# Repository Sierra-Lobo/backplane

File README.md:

# backplane

Sierra Lobo's 1.5U Cubesat Backplane

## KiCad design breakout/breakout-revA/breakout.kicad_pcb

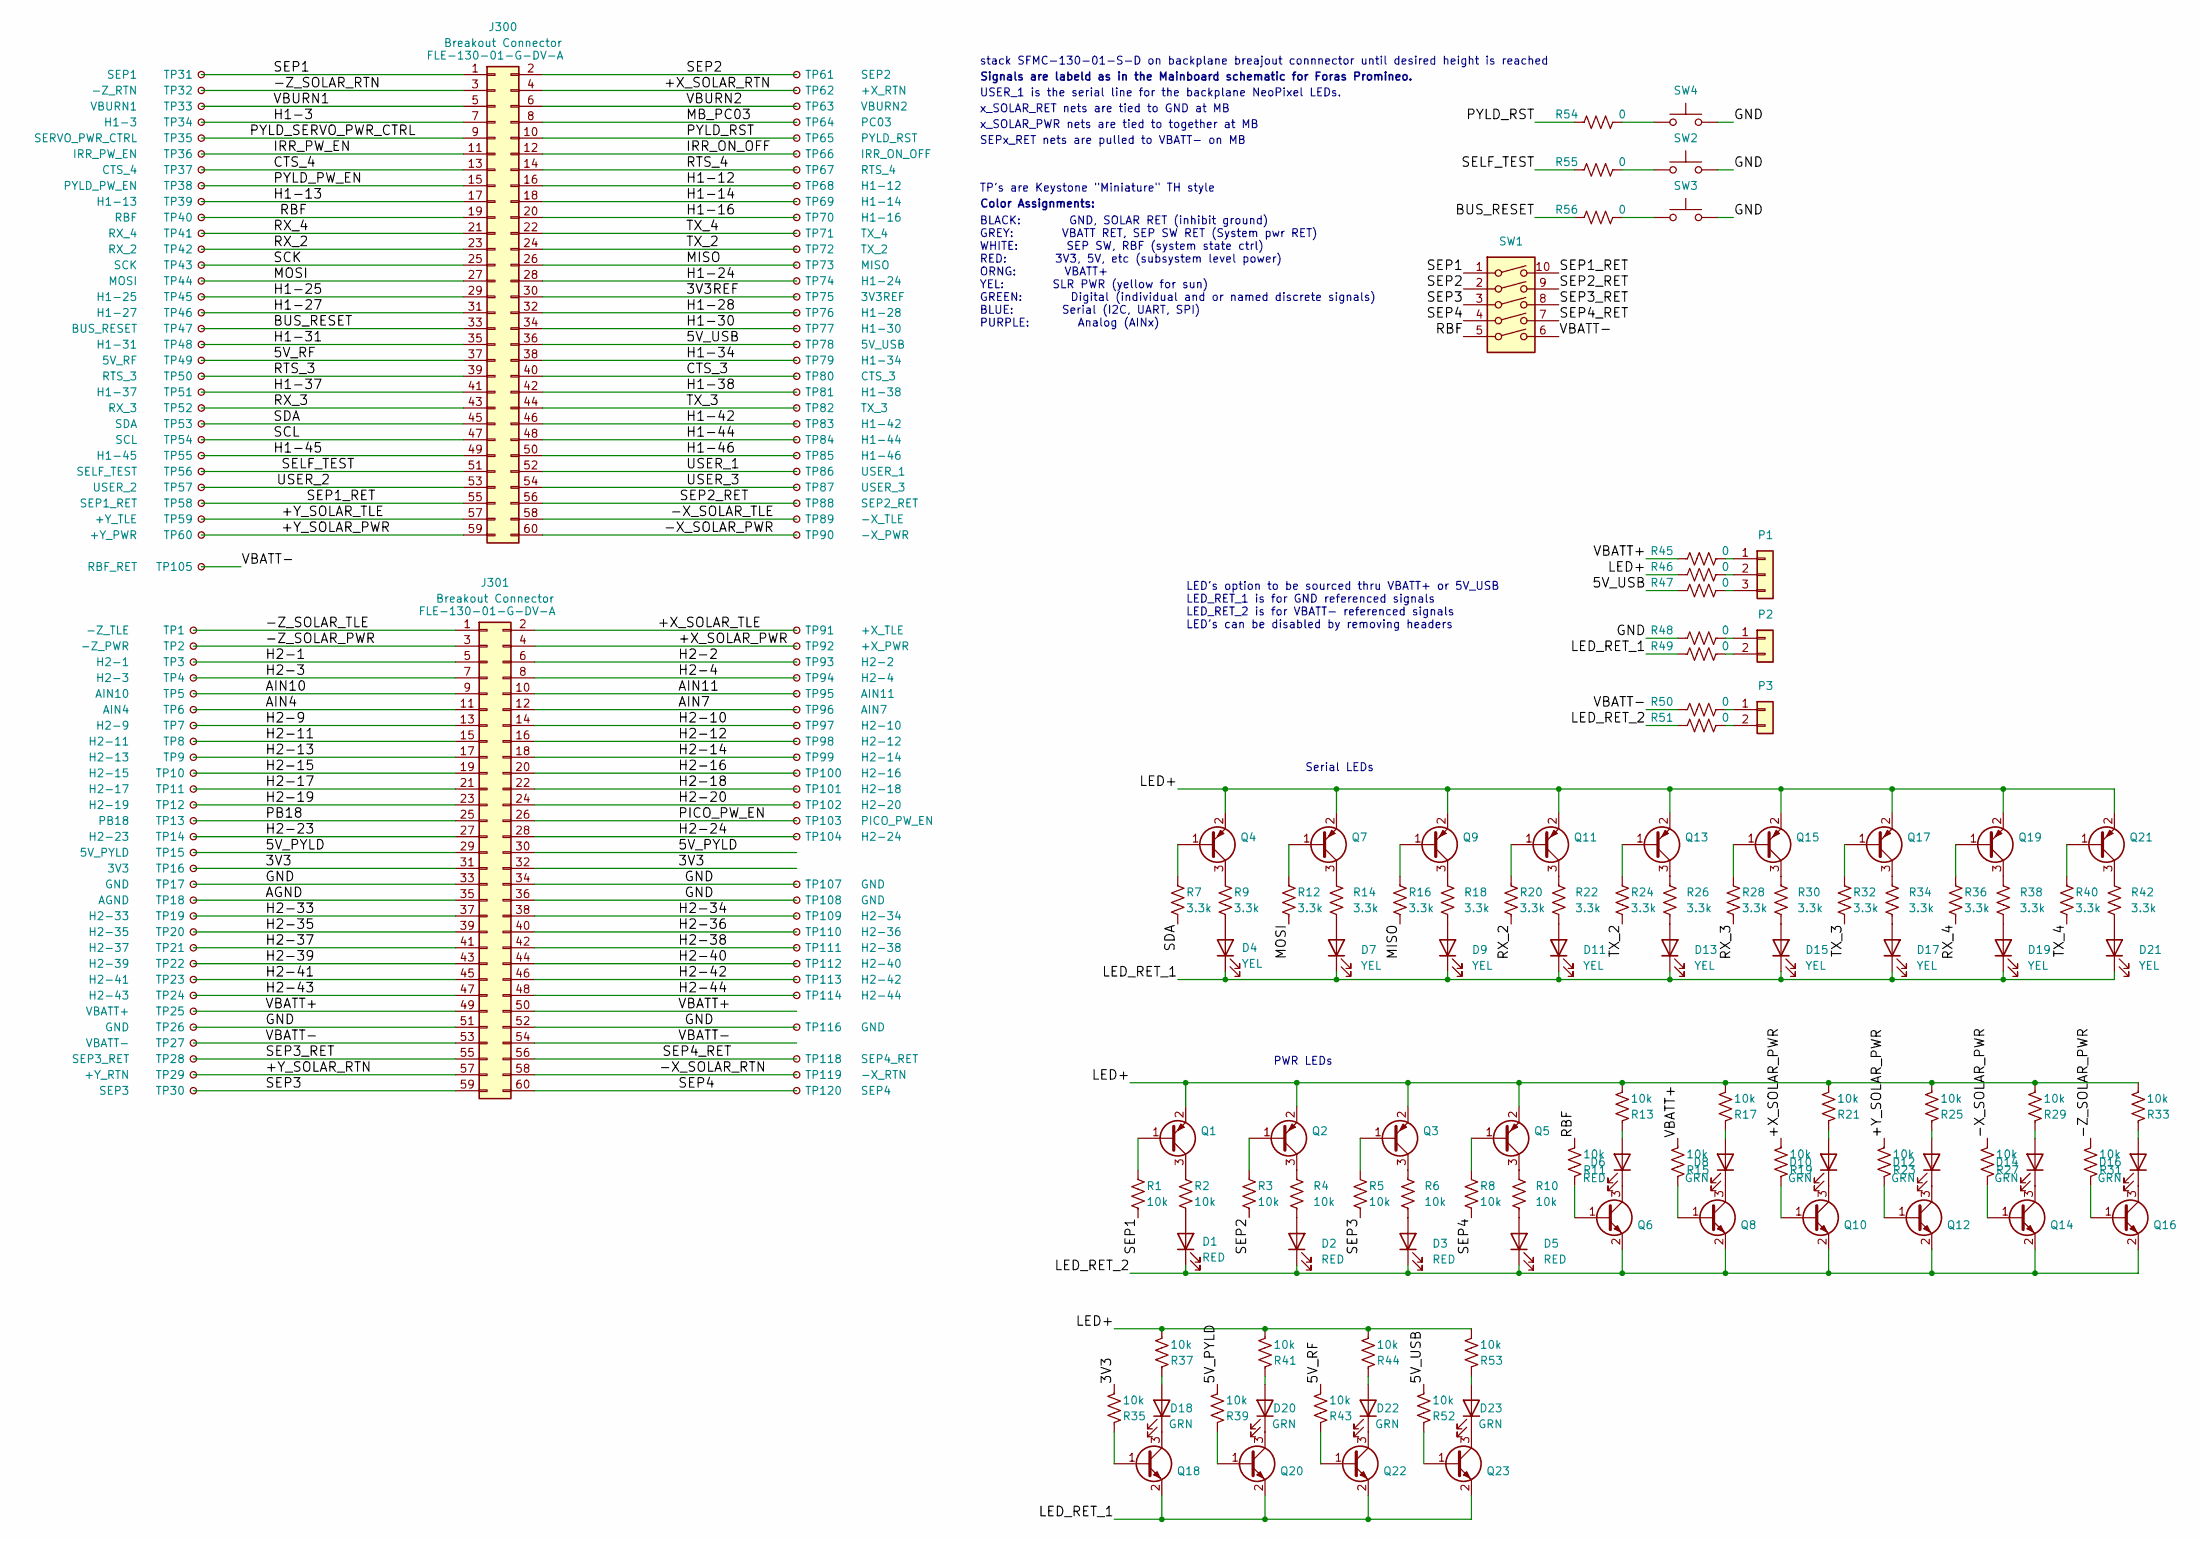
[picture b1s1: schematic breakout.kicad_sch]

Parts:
D1, D2, D3, D5, D6: RED; LED_0603_1608Metric_Pad1.05x0.95mm_HandSolder
D4, D7, D9, D11, D13, D15, D17, D19, D21: YEL; LED_0603_1608Metric_Pad1.05x0.95mm_HandSolder
D8, D10, D12, D14, D16, D18, D20, D22, D23: GRN; LED_0603_1608Metric_Pad1.05x0.95mm_HandSolder
J300, J301: Breakout Connector; SAMTEC_CLP-130-02-X-D-BE-A-P-TR; Manufacturer Part Numbe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 FLE-130-01-G-DV-A
P1: Conn_01x03; PinHeader_1x03_P2.54mm_Vertical
P2, P3: Conn_01x03; PinHeader_1x02_P2.54mm_Vertical
Q1, Q2, Q3, Q4, Q5, Q7, Q9, Q11, Q13, Q15, Q17, Q19, Q21: MMBT3906-7-F; SOT-23
Q6, Q8, Q10, Q12, Q14, Q16, Q18, Q20, Q22, Q23: MMBT3904-TP; SOT-23
R1, R2, R3, R4, R5, R6, R8, R10, R11, R13, R15, R17, R19, R21, R23, R25, R27, R29, R31, R33, R35, R37, R39, R41, R43, R44, R52, R53: 10k; R_0603_1608Metric_Pad0.98x0.95mm_HandSolder
R7, R9, R12, R14, R16, R18, R20, R22, R24, R26, R28, R30, R32, R34, R36, R38, R40, R42: 3.3k; R_0603_1608Metric_Pad0.98x0.95mm_HandSolder
R45, R46, R47, R48, R49, R50, R51, R54, R55, R56: 0; R_0603_1608Metric_Pad0.98x0.95mm_HandSolder
SW1: A6SN-5104; SW_DIP_SPSTx05_Slide_Omron_A6S-510x_W8.9mm_P2.54mm
SW2, SW3, SW4: PTS810 SJS 250 SMTR LFS; SW_SPST_PTS810
TP1: -Z_TLE; TestPoint_Keystone_5000-5004_Miniature
TP2: -Z_PWR; TestPoint_Keystone_5010-5014_Multipurpose
TP3: H2-1; TestPoint_THTPad_D1.0mm_Drill0.5mm
TP4: H2-3; TestPoint_THTPad_D1.0mm_Drill0.5mm
TP5: AIN10; TestPoint_Keystone_5000-5004_Miniature
TP6: AIN4; TestPoint_Keystone_5000-5004_Miniature
TP7: H2-9; TestPoint_THTPad_D1.0mm_Drill0.5mm
TP8: H2-11; TestPoint_THTPad_D1.0mm_Drill0.5mm
TP9: H2-13; TestPoint_THTPad_D1.0mm_Drill0.5mm
TP10: H2-15; TestPoint_THTPad_D1.0mm_Drill0.5mm
TP11: H2-17; TestPoint_THTPad_D1.0mm_Drill0.5mm
TP12: H2-19; TestPoint_THTPad_D1.0mm_Drill0.5mm
TP13: PB18; TestPoint_Keystone_5000-5004_Miniature
TP14: H2-23; TestPoint_THTPad_D1.0mm_Drill0.5mm
TP15: 5V_PYLD; TestPoint_Keystone_5010-5014_Multipurpose
TP16: 3V3; TestPoint_Keystone_5010-5014_Multipurpose
TP17, TP26, TP107, TP108: GND; TestPoint_Keystone_5010-5014_Multipurpose
TP18: AGND; TestPoint_Keystone_5000-5004_Miniature
TP19: H2-33; TestPoint_THTPad_D1.0mm_Drill0.5mm
TP20: H2-35; TestPoint_THTPad_D1.0mm_Drill0.5mm
TP21: H2-37; TestPoint_THTPad_D1.0mm_Drill0.5mm
TP22: H2-39; TestPoint_THTPad_D1.0mm_Drill0.5mm
TP23: H2-41; TestPoint_THTPad_D1.0mm_Drill0.5mm
TP24: H2-43; TestPoint_THTPad_D1.0mm_Drill0.5mm
TP25: VBATT+; TestPoint_Keystone_5010-5014_Multipurpose
TP27: VBATT-; TestPoint_Keystone_5010-5014_Multipurpose
TP28: SEP3_RET; TestPoint_Keystone_5000-5004_Miniature
TP29: +Y_RTN; TestPoint_Keystone_5010-5014_Multipurpose
TP30: SEP3; TestPoint_Keystone_5000-5004_Miniature
TP31: SEP1; TestPoint_Keystone_5000-5004_Miniature
TP32: -Z_RTN; TestPoint_Keystone_5010-5014_Multipurpose
TP33: VBURN1; TestPoint_Keystone_5000-5004_Miniature
TP34: H1-3; TestPoint_THTPad_D1.0mm_Drill0.5mm
TP35: SERVO_PWR_CTRL; TestPoint_Keystone_5000-5004_Miniature
TP36: IRR_PW_EN; TestPoint_Keystone_5000-5004_Miniature
TP37: CTS_4; TestPoint_Keystone_5000-5004_Miniature
TP38: PYLD_PW_EN; TestPoint_Keystone_5000-5004_Miniature
TP39: H1-13; TestPoint_THTPad_D1.0mm_Drill0.5mm
TP40: RBF; TestPoint_Keystone_5000-5004_Miniature
TP41: RX_4; TestPoint_Keystone_5000-5004_Miniature
TP42: RX_2; TestPoint_Keystone_5000-5004_Miniature
TP43: SCK; TestPoint_Keystone_5000-5004_Miniature
TP44: MOSI; TestPoint_Keystone_5000-5004_Miniature
TP45: H1-25; TestPoint_THTPad_D1.0mm_Drill0.5mm
TP46: H1-27; TestPoint_THTPad_D1.0mm_Drill0.5mm
TP47: BUS_RESET; TestPoint_Keystone_5000-5004_Miniature
TP48: H1-31; TestPoint_THTPad_D1.0mm_Drill0.5mm
TP49: 5V_RF; TestPoint_Keystone_5010-5014_Multipurpose
TP50: RTS_3; TestPoint_Keystone_5000-5004_Miniature
TP51: H1-37; TestPoint_THTPad_D1.0mm_Drill0.5mm
TP52: RX_3; TestPoint_Keystone_5000-5004_Miniature
TP53: SDA; TestPoint_Keystone_5000-5004_Miniature
TP54: SCL; TestPoint_Keystone_5000-5004_Miniature
TP55: H1-45; TestPoint_THTPad_D1.0mm_Drill0.5mm
TP56: SELF_TEST; TestPoint_Keystone_5000-5004_Miniature
TP57: USER_2; TestPoint_Keystone_5000-5004_Miniature
TP58: SEP1_RET; TestPoint_Keystone_5000-5004_Miniature
TP59: +Y_TLE; TestPoint_Keystone_5000-5004_Miniature
TP60: +Y_PWR; TestPoint_Keystone_5010-5014_Multipurpose
TP61: SEP2; TestPoint_Keystone_5000-5004_Miniature
TP62: +X_RTN; TestPoint_Keystone_5010-5014_Multipurpose
TP63: VBURN2; TestPoint_Keystone_5000-5004_Miniature
TP64: PC03; TestPoint_Keystone_5000-5004_Miniature
TP65: PYLD_RST; TestPoint_Keystone_5000-5004_Miniature
TP66: IRR_ON_OFF; TestPoint_Keystone_5000-5004_Miniature
TP67: RTS_4; TestPoint_Keystone_5000-5004_Miniature
TP68: H1-12; TestPoint_THTPad_D1.0mm_Drill0.5mm
TP69: H1-14; TestPoint_THTPad_D1.0mm_Drill0.5mm
TP70: H1-16; TestPoint_THTPad_D1.0mm_Drill0.5mm
TP71: TX_4; TestPoint_Keystone_5000-5004_Miniature
TP72: TX_2; TestPoint_Keystone_5000-5004_Miniature
TP73: MISO; TestPoint_Keystone_5000-5004_Miniature
TP74: H1-24; TestPoint_THTPad_D1.0mm_Drill0.5mm
TP75: 3V3REF; TestPoint_Keystone_5000-5004_Miniature
TP76: H1-28; TestPoint_THTPad_D1.0mm_Drill0.5mm
TP77: H1-30; TestPoint_THTPad_D1.0mm_Drill0.5mm
TP78: 5V_USB; TestPoint_Keystone_5010-5014_Multipurpose
TP79: H1-34; TestPoint_THTPad_D1.0mm_Drill0.5mm
TP80: CTS_3; TestPoint_Keystone_5000-5004_Miniature
TP81: H1-38; TestPoint_THTPad_D1.0mm_Drill0.5mm
TP82: TX_3; TestPoint_Keystone_5000-5004_Miniature
TP83: H1-42; TestPoint_THTPad_D1.0mm_Drill0.5mm
TP84: H1-44; TestPoint_THTPad_D1.0mm_Drill0.5mm
TP85: H1-46; TestPoint_THTPad_D1.0mm_Drill0.5mm
TP86: USER_1; TestPoint_Keystone_5000-5004_Miniature
TP87: USER_3; TestPoint_Keystone_5000-5004_Miniature
TP88: SEP2_RET; TestPoint_Keystone_5000-5004_Miniature
TP89: -X_TLE; TestPoint_Keystone_5000-5004_Miniature
TP90: -X_PWR; TestPoint_Keystone_5010-5014_Multipurpose
TP91: +X_TLE; TestPoint_Keystone_5000-5004_Miniature
TP92: +X_PWR; TestPoint_Keystone_5010-5014_Multipurpose
TP93: H2-2; TestPoint_THTPad_D1.0mm_Drill0.5mm
TP94: H2-4; TestPoint_THTPad_D1.0mm_Drill0.5mm
TP95: AIN11; TestPoint_Keystone_5000-5004_Miniature
TP96: AIN7; TestPoint_Keystone_5000-5004_Miniature
TP97: H2-10; TestPoint_THTPad_D1.0mm_Drill0.5mm
TP98: H2-12; TestPoint_THTPad_D1.0mm_Drill0.5mm
TP99: H2-14; TestPoint_THTPad_D1.0mm_Drill0.5mm
TP100: H2-16; TestPoint_THTPad_D1.0mm_Drill0.5mm
TP101: H2-18; TestPoint_THTPad_D1.0mm_Drill0.5mm
TP102: H2-20; TestPoint_THTPad_D1.0mm_Drill0.5mm
TP103: PICO_PW_EN; TestPoint_Keystone_5000-5004_Miniature
TP104: H2-24; TestPoint_THTPad_D1.0mm_Drill0.5mm
TP105: RBF_RET; TestPoint_Keystone_5000-5004_Miniature
TP109: H2-34; TestPoint_THTPad_D1.0mm_Drill0.5mm
TP110: H2-36; TestPoint_THTPad_D1.0mm_Drill0.5mm
TP111: H2-38; TestPoint_THTPad_D1.0mm_Drill0.5mm
TP112: H2-40; TestPoint_THTPad_D1.0mm_Drill0.5mm
TP113: H2-42; TestPoint_THTPad_D1.0mm_Drill0.5mm
TP114: H2-44; TestPoint_THTPad_D1.0mm_Drill0.5mm
TP116: GND; TestPoint_Keystone_5000-5004_Miniature
TP118: SEP4_RET; TestPoint_Keystone_5000-5004_Miniature
TP119: -X_RTN; TestPoint_Keystone_5010-5014_Multipurpose
TP120: SEP4; TestPoint_Keystone_5000-5004_Miniature

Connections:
/3V3: J301.31, J301.32, R35.1, TP16.1
/3V3REF: J300.30, TP75.1
/5V_PYLD: J301.29, J301.30, R39.1, TP15.1
/5V_RF: J300.37, R43.1, TP49.1
/5V_USB: J300.36, R47.1, R52.1, TP78.1
/+X_SOLAR_PWR: J301.4, R19.1, TP92.1
/+X_SOLAR_RTN: J300.4, TP62.1
/+X_SOLAR_TLE: J301.2, TP91.1
/+Y_SOLAR_PWR: J300.59, R23.1, TP60.1
/+Y_SOLAR_RTN: J301.57, TP29.1
/+Y_SOLAR_TLE: J300.57, TP59.1
/-X_SOLAR_PWR: J300.60, R27.1, TP90.1
/-X_SOLAR_RTN: J301.58, TP119.1
/-X_SOLAR_TLE: J300.58, TP89.1
/-Z_SOLAR_PWR: J301.3, R31.1, TP2.1
/-Z_SOLAR_RTN: J300.3, TP32.1
/-Z_SOLAR_TLE: J301.1, TP1.1
/AGND: J301.35, TP18.1
/AIN4: J301.11, TP6.1
/AIN7: J301.12, TP96.1
/AIN10: J301.9, TP5.1
/AIN11: J301.10, TP95.1
/BUS_RESET: J300.33, R56.1, TP47.1
/CTS_3: J300.40, TP80.1
/CTS_4: J300.13, TP37.1
/GND: J301.33, J301.34, J301.36, J301.51, J301.52, R48.1, SW2.2, SW3.2, SW4.2, TP17.1, TP26.1, TP107.1, TP108.1, TP116.1; also elsewhere on the board
/H1-3: J300.7, TP34.1
/H1-12: J300.16, TP68.1
/H1-13: J300.17, TP39.1
/H1-14: J300.18, TP69.1
/H1-16: J300.20, TP70.1
/H1-24: J300.28, TP74.1
/H1-25: J300.29, TP45.1
/H1-27: J300.31, TP46.1
/H1-28: J300.32, TP76.1
/H1-30: J300.34, TP77.1
/H1-31: J300.35, TP48.1
/H1-34: J300.38, TP79.1
/H1-37: J300.41, TP51.1
/H1-38: J300.42, TP81.1
/H1-42: J300.46, TP83.1
/H1-44: J300.48, TP84.1
/H1-45: J300.49, TP55.1
/H1-46: J300.50, TP85.1
/H2-1: J301.5, TP3.1
/H2-2: J301.6, TP93.1
/H2-3: J301.7, TP4.1
/H2-4: J301.8, TP94.1
/H2-9: J301.13, TP7.1
/H2-10: J301.14, TP97.1
/H2-11: J301.15, TP8.1
/H2-12: J301.16, TP98.1
/H2-13: J301.17, TP9.1
/H2-14: J301.18, TP99.1
/H2-15: J301.19, TP10.1
/H2-16: J301.20, TP100.1
/H2-17: J301.21, TP11.1
/H2-18: J301.22, TP101.1
/H2-19: J301.23, TP12.1
/H2-20: J301.24, TP102.1
/H2-23: J301.27, TP14.1
/H2-24: J301.28, TP104.1
/H2-33: J301.37, TP19.1
/H2-34: J301.38, TP109.1
/H2-35: J301.39, TP20.1
/H2-36: J301.40, TP110.1
/H2-37: J301.41, TP21.1
/H2-38: J301.42, TP111.1
/H2-39: J301.43, TP22.1
/H2-40: J301.44, TP112.1
/H2-41: J301.45, TP23.1
/H2-42: J301.46, TP113.1
/H2-43: J301.47, TP24.1
/H2-44: J301.48, TP114.1
/IRR_ON_OFF: J300.12, TP66.1
/IRR_PW_EN: J300.11, TP36.1
/LED+: Q1.2 (E), Q2.2 (E), Q3.2 (E), Q4.2 (E), Q5.2 (E), Q7.2 (E), Q9.2 (E), Q11.2 (E), Q13.2 (E), Q15.2 (E), Q17.2 (E), Q19.2 (E), Q21.2 (E), R13.2, R17.2, R21.2, R25.2, R29.2, R33.2, R37.2, R41.2, R44.2, R46.1, R53.2
/LED_RET_1: D4.1 (K), D7.1 (K), D9.1 (K), D11.1 (K), D13.1 (K), D15.1 (K), D17.1 (K), D19.1 (K), D21.1 (K), Q18.2 (E), Q20.2 (E), Q22.2 (E), Q23.2 (E), R49.1
/LED_RET_2: D1.1 (K), D2.1 (K), D3.1 (K), D5.1 (K), Q6.2 (E), Q8.2 (E), Q10.2 (E), Q12.2 (E), Q14.2 (E), Q16.2 (E), R51.1
/MB_PC03: J300.8, TP64.1
/MISO: J300.26, R16.1, TP73.1
/MOSI: J300.27, R12.1, TP44.1
/PB18: J301.25, TP13.1
/PICO_PW_EN: J301.26, TP103.1
/PYLD_PW_EN: J300.15, TP38.1
/PYLD_RST: J300.10, R54.1, TP65.1
/PYLD_SERVO_PWR_CTRL: J300.9, TP35.1
/RBF: J300.19, R11.1, SW1.5, TP40.1
/RTS_3: J300.39, TP50.1
/RTS_4: J300.14, TP67.1
/RX_2: J300.23, R20.1, TP42.1
/RX_3: J300.43, R28.1, TP52.1
/RX_4: J300.21, R36.1, TP41.1
/SCK: J300.25, TP43.1
/SCL: J300.47, TP54.1
/SDA: J300.45, R7.1, TP53.1
/SELF_TEST: J300.51, R55.1, TP56.1
/SEP1: J300.1, R1.1, SW1.1, TP31.1
/SEP1_RET: J300.55, SW1.10, TP58.1
/SEP2: J300.2, R3.1, SW1.2, TP61.1
/SEP2_RET: J300.56, SW1.9, TP88.1
/SEP3: J301.59, R5.1, SW1.3, TP30.1
/SEP3_RET: J301.55, SW1.8, TP28.1
/SEP4: J301.60, R8.1, SW1.4, TP120.1
/SEP4_RET: J301.56, SW1.7, TP118.1
/TX_2: J300.24, R24.1, TP72.1
/TX_3: J300.44, R32.1, TP82.1
/TX_4: J300.22, R40.1, TP71.1
/USER_1: J300.52, TP86.1
/USER_2: J300.53, TP57.1
/USER_3: J300.54, TP87.1
/VBATT+: J301.49, J301.50, R15.1, R45.1, TP25.1
/VBATT-: J301.53, J301.54, R50.1, SW1.6, TP27.1, TP105.1
/VBURN1: J300.5, TP33.1
/VBURN2: J300.6, TP63.1
unnamed: D1.2 (A), R2.2
unnamed: D2.2 (A), R4.2
unnamed: D3.2 (A), R6.2
unnamed: D4.2 (A), R9.2
unnamed: D5.2 (A), R10.2
unnamed: D6.1 (K), Q6.3 (C)
unnamed: D6.2 (A), R13.1
unnamed: D7.2 (A), R14.2
unnamed: D8.1 (K), Q8.3 (C)
unnamed: D8.2 (A), R17.1
unnamed: D9.2 (A), R18.2
unnamed: D10.1 (K), Q10.3 (C)
unnamed: D10.2 (A), R21.1
unnamed: D11.2 (A), R22.2
unnamed: D12.1 (K), Q12.3 (C)
unnamed: D12.2 (A), R25.1
unnamed: D13.2 (A), R26.2
unnamed: D14.1 (K), Q14.3 (C)
unnamed: D14.2 (A), R29.1
unnamed: D15.2 (A), R30.2
unnamed: D16.1 (K), Q16.3 (C)
unnamed: D16.2 (A), R33.1
unnamed: D17.2 (A), R34.2
unnamed: D18.1 (K), Q18.3 (C)
unnamed: D18.2 (A), R37.1
unnamed: D19.2 (A), R38.2
unnamed: D20.1 (K), Q20.3 (C)
unnamed: D20.2 (A), R41.1
unnamed: D21.2 (A), R42.2
unnamed: D22.1 (K), Q22.3 (C)
unnamed: D22.2 (A), R44.1
unnamed: D23.1 (K), Q23.3 (C)
unnamed: D23.2 (A), R53.1
unnamed: P1.1, R45.2
unnamed: P1.2, R46.2
unnamed: P1.3, R47.2
unnamed: P2.1, R48.2
unnamed: P2.2, R49.2
unnamed: P3.1, R50.2
unnamed: P3.2, R51.2
unnamed: Q1.1 (B), R1.2
unnamed: Q1.3 (C), R2.1
unnamed: Q2.1 (B), R3.2
unnamed: Q2.3 (C), R4.1
unnamed: Q3.1 (B), R5.2
unnamed: Q3.3 (C), R6.1
unnamed: Q4.1 (B), R7.2
unnamed: Q4.3 (C), R9.1
unnamed: Q5.1 (B), R8.2
unnamed: Q5.3 (C), R10.1
unnamed: Q6.1 (B), R11.2
unnamed: Q7.1 (B), R12.2
unnamed: Q7.3 (C), R14.1
unnamed: Q8.1 (B), R15.2
unnamed: Q9.1 (B), R16.2
unnamed: Q9.3 (C), R18.1
unnamed: Q10.1 (B), R19.2
unnamed: Q11.1 (B), R20.2
unnamed: Q11.3 (C), R22.1
unnamed: Q12.1 (B), R23.2
unnamed: Q13.1 (B), R24.2
unnamed: Q13.3 (C), R26.1
unnamed: Q14.1 (B), R27.2
unnamed: Q15.1 (B), R28.2
unnamed: Q15.3 (C), R30.1
unnamed: Q16.1 (B), R31.2
unnamed: Q17.1 (B), R32.2
unnamed: Q17.3 (C), R34.1
unnamed: Q18.1 (B), R35.2
unnamed: Q19.1 (B), R36.2
unnamed: Q19.3 (C), R38.1
unnamed: Q20.1 (B), R39.2
unnamed: Q21.1 (B), R40.2
unnamed: Q21.3 (C), R42.1
unnamed: Q22.1 (B), R43.2
unnamed: Q23.1 (B), R52.2
unnamed: R54.2, SW4.1
unnamed: R55.2, SW2.1
unnamed: R56.2, SW3.1

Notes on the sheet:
LED's option to be sourced thru VBATT+ or 5V_USB LED_RET_1 is for GND referenced signals LED_RET_2 is for VBATT- referenced signals LED's can be disabled by removing headers
USER_1 is the serial line for the backplane NeoPixel LEDs.
x_SOLAR_RET nets are tied to GND at MB
stack SFMC-130-01-S-D on backplane breajout connnector until desired height is reached
x_SOLAR_PWR nets are tied to together at MB
Color Assignments:
SEPx_RET nets are pulled to VBATT- on MB
Signals are labeld as in the Mainboard schematic for Foras Promineo.
Serial LEDs
TP's are Keystone "Miniature" TH style
PWR LEDs
BLACK: GND, SOLAR RET (inhibit ground) GREY: VBATT RET, SEP SW RET (System pwr RET) WHITE: SEP SW, RBF (system state ctrl) RED: 3V3, 5V, etc (subsystem level power) ORNG: VBATT+ YEL: SLR PWR (yellow for sun) GREEN: Digital (individual and or named discrete signals) BLUE: Serial (I2C, UART, SPI) PUR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

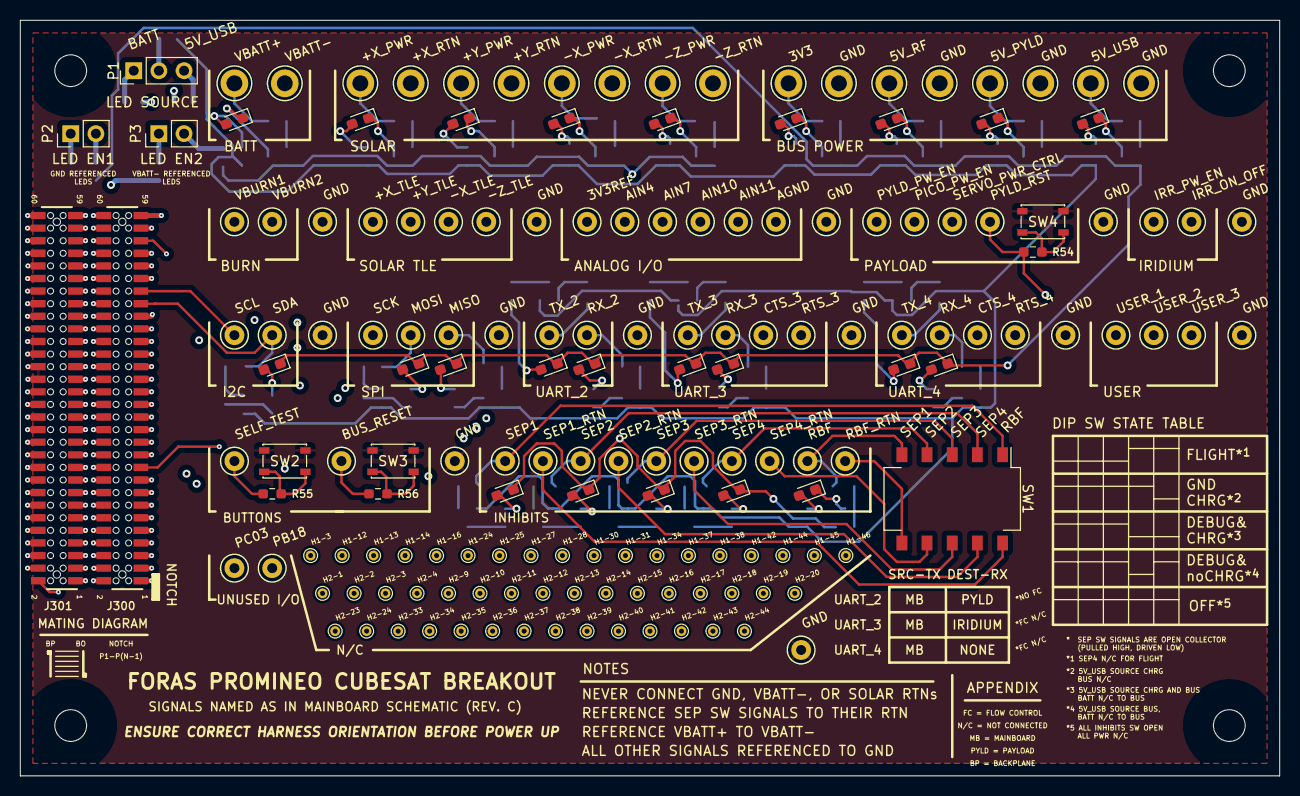
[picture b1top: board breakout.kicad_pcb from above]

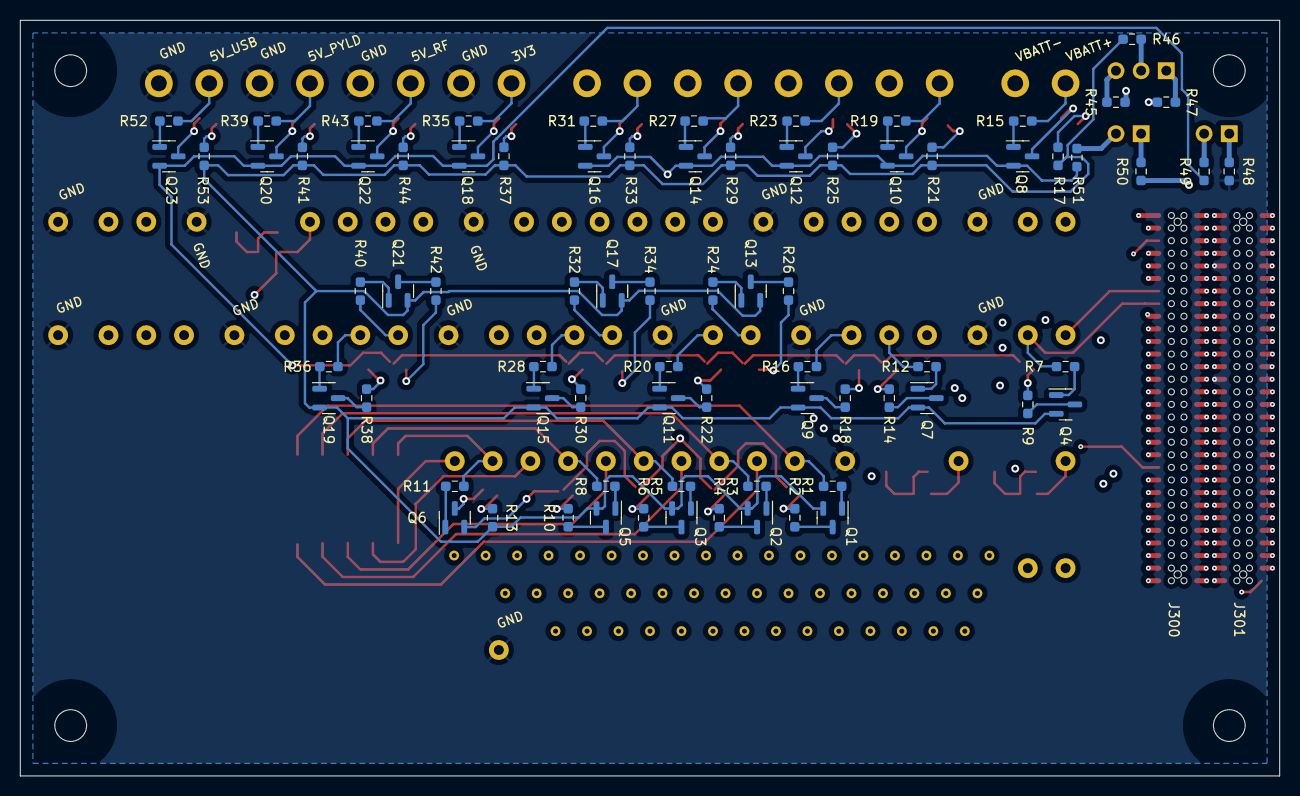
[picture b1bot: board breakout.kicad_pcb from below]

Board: 8 copper layers, 127.0 x 76.2 mm, 240 parts (76 on the bottom side), 194 nets.

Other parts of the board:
TP116#2, TP116#3, TP116#4, TP116#5, TP116#6, TP116#7, TP116#8, TP116#9, TP116#10, TP116#11, TP116#12, TP116#13: GND; TestPoint_Keystone_5000-5004_Miniature

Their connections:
/GND: TP116#2.1, TP116#3.1, TP116#4.1, TP116#5.1, TP116#6.1, TP116#7.1, TP116#8.1, TP116#9.1, TP116#10.1, TP116#11.1, TP116#12.1, TP116#13.1; also elsewhere on the board

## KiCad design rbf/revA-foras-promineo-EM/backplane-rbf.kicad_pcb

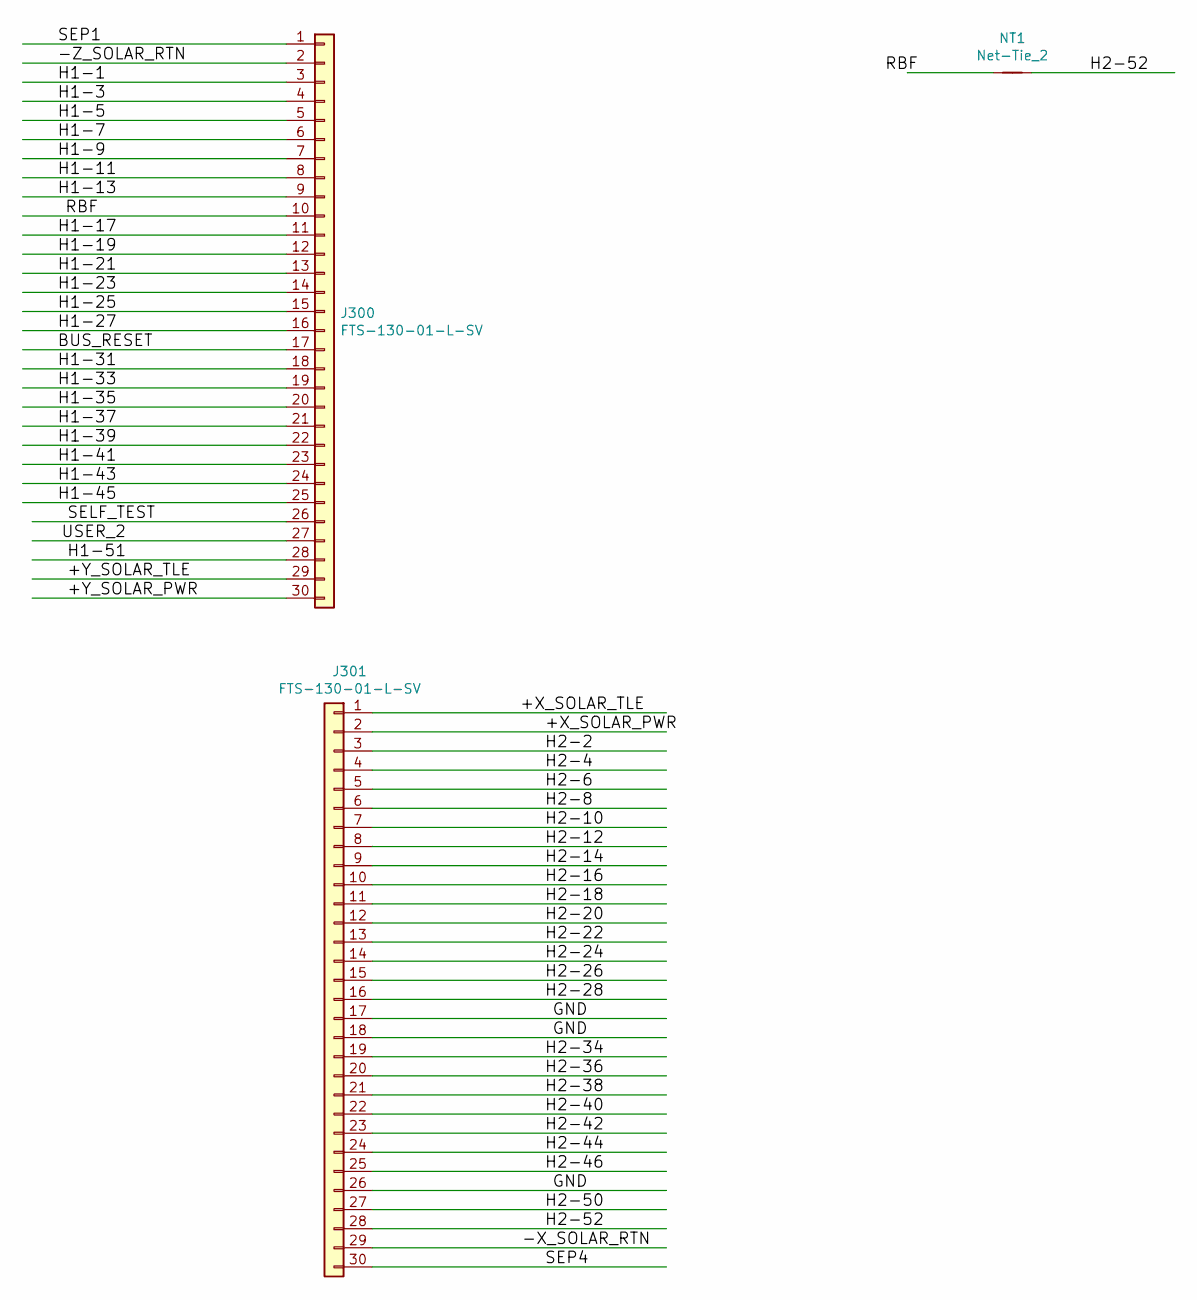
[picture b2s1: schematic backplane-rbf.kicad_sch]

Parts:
J300, J301: FTS-130-01-L-SV
NT1: Net-Tie_2; NetTie-2_SMD_Pad0.25mm

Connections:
/+X_SOLAR_PWR: J301.2
/+X_SOLAR_TLE: J301.1
/+Y_SOLAR_PWR: J300.30
/+Y_SOLAR_TLE: J300.29
/-X_SOLAR_RTN: J301.29
/-Z_SOLAR_RTN: J300.2
/BUS_RESET: J300.17
/GND: J301.17, J301.18, J301.26
/H1-1: J300.3
/H1-3: J300.4
/H1-5: J300.5
/H1-7: J300.6
/H1-9: J300.7
/H1-11: J300.8
/H1-13: J300.9
/H1-17: J300.11
/H1-19: J300.12
/H1-21: J300.13
/H1-23: J300.14
/H1-25: J300.15
/H1-27: J300.16
/H1-31: J300.18
/H1-33: J300.19
/H1-35: J300.20
/H1-37: J300.21
/H1-39: J300.22
/H1-41: J300.23
/H1-43: J300.24
/H1-45: J300.25
/H1-51: J300.28
/H2-2: J301.3
/H2-4: J301.4
/H2-6: J301.5
/H2-8: J301.6
/H2-10: J301.7
/H2-12: J301.8
/H2-14: J301.9
/H2-16: J301.10
/H2-18: J301.11
/H2-20: J301.12
/H2-22: J301.13
/H2-24: J301.14
/H2-26: J301.15
/H2-28: J301.16
/H2-34: J301.19
/H2-36: J301.20
/H2-38: J301.21
/H2-40: J301.22
/H2-42: J301.23
/H2-44: J301.24
/H2-46: J301.25
/H2-50: J301.27
/H2-52: J301.28, NT1.2
/RBF: J300.10, NT1.1
/SELF_TEST: J300.26
/SEP1: J300.1
/SEP4: J301.30
/USER_2: J300.27

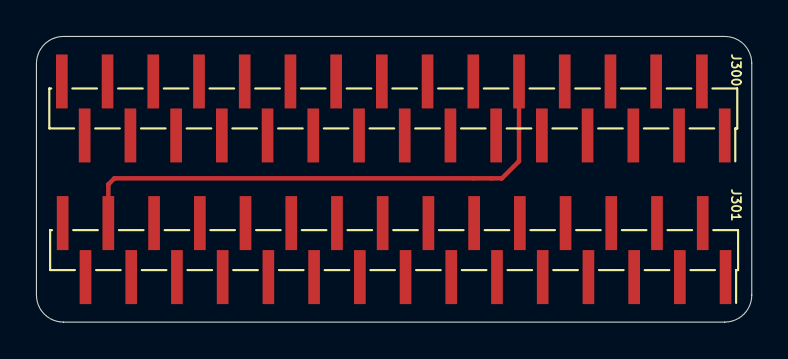
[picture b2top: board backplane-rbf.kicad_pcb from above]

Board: 2 copper layers, 39.7 x 15.9 mm, 3 parts (0 on the bottom side), 3 nets.

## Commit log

2021-12-10 kicad files init commit
2021-12-10 Add files via upload
    initial revA1
2021-12-17 final changes before ordering
2021-12-17 adding project files for adapter boards
2021-12-18 changed breakout connector
2021-12-18 fab data for new connector
2021-12-19 backplane sepsw emulator board
2021-12-19 made backplane breakout fpc
2021-12-20 breakout-big
2021-12-20 changed to 2x30 1.27mm headers
2021-12-21 8mil/8mil trace/space
2021-12-21 breakout connector
2021-12-21 fab files to pcbway
2021-12-22 tested rbf fit
2021-12-22 backplane-breakout-big
2021-12-27 pcbway eng ?s
2022-01-03 routed more
2022-01-04 updated .pos files for fabrication
2022-01-04 completion push
2022-01-05 fab files generated 2 pcbway
2022-01-25 minor bom issues corrected
2022-02-23 bom change
2022-02-23 rearranged folders
2022-03-17 update gitignore
2022-05-10 revC FM
2022-05-12 corrected gerbers for FM
2022-05-13 extracted 3d model
2022-05-19 updated fab notes
2022-09-09 updated RBF to correct pin
2023-01-12 init breakout commit
2023-01-13 updated silk screen, bom, and sub J301.
2023-01-24 Fixed pinout of solar panel connectors on backplane
    pinout didnt match solar panels. pins 7 and 8 on solar panels aren't used. pin 7 is an extra tlm connection, pin 8 is an extra chs connection.
2023-03-16 added rbf_ret net, added capability for neopixels on BP cards, added jumpers to bypass this
2023-03-21 renamed rev folders
2023-03-22 moved /breakout-big to separate repo
2023-03-22 moved backplane-rbf to its own repo
2023-03-22 moved breakout to its own repo
2023-03-24 updated layout for fm.
2023-03-24 removed old files
2023-05-30 working post-review changes
2023-05-31 revC commit
2023-06-01 generated fab files
2023-06-01 added some datasheets
2023-06-08 bom updated
2023-06-22 retrieved original revC, latest is now C1
